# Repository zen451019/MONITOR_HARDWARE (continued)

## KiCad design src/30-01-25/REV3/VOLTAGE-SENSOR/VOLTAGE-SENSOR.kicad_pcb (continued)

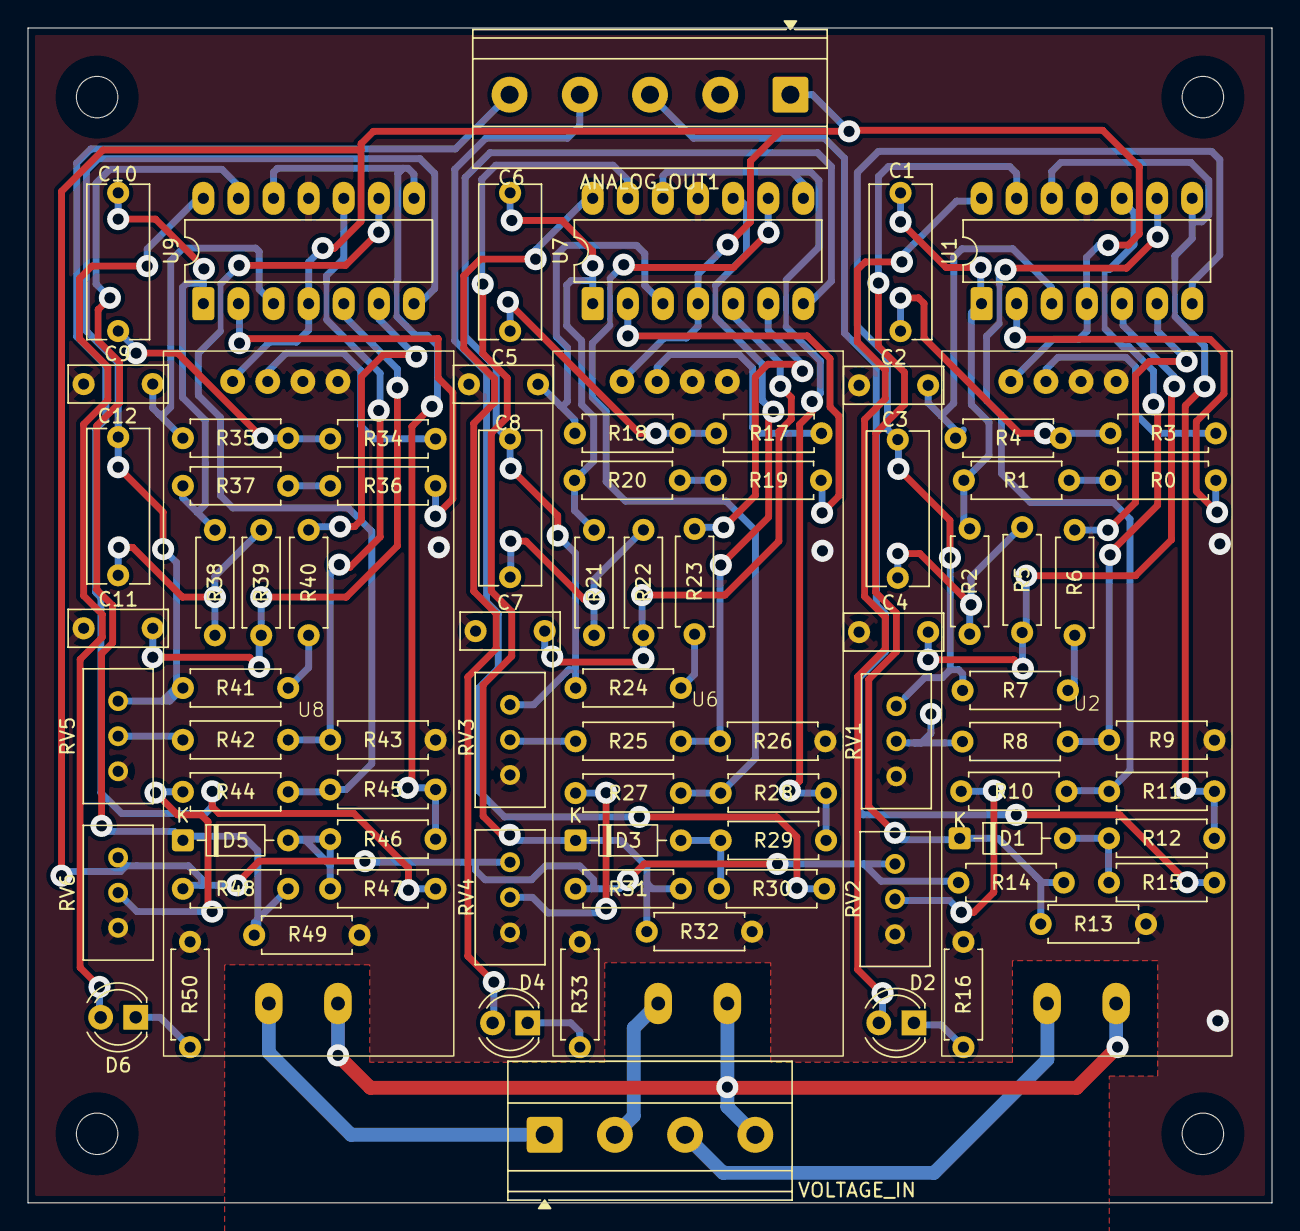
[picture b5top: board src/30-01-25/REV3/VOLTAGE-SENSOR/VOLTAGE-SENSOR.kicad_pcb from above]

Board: 2 copper layers, 90.0 x 85.0 mm, 83 parts (0 on the bottom side), 69 nets.

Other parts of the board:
VOLTAGE_IN: SCREW_TERMINAL_4; TerminalBlock_Phoenix_MKDS-1,5-4-5.08_1x04_P5.08mm_Horizont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

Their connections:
LINE1: VOLTAGE_IN.1; also elsewhere on the board
LINE2: VOLTAGE_IN.2; also elsewhere on the board
LINE3: VOLTAGE_IN.3; also elsewhere on the board
NEUTRAL: VOLTAGE_IN.4; also elsewhere on the board

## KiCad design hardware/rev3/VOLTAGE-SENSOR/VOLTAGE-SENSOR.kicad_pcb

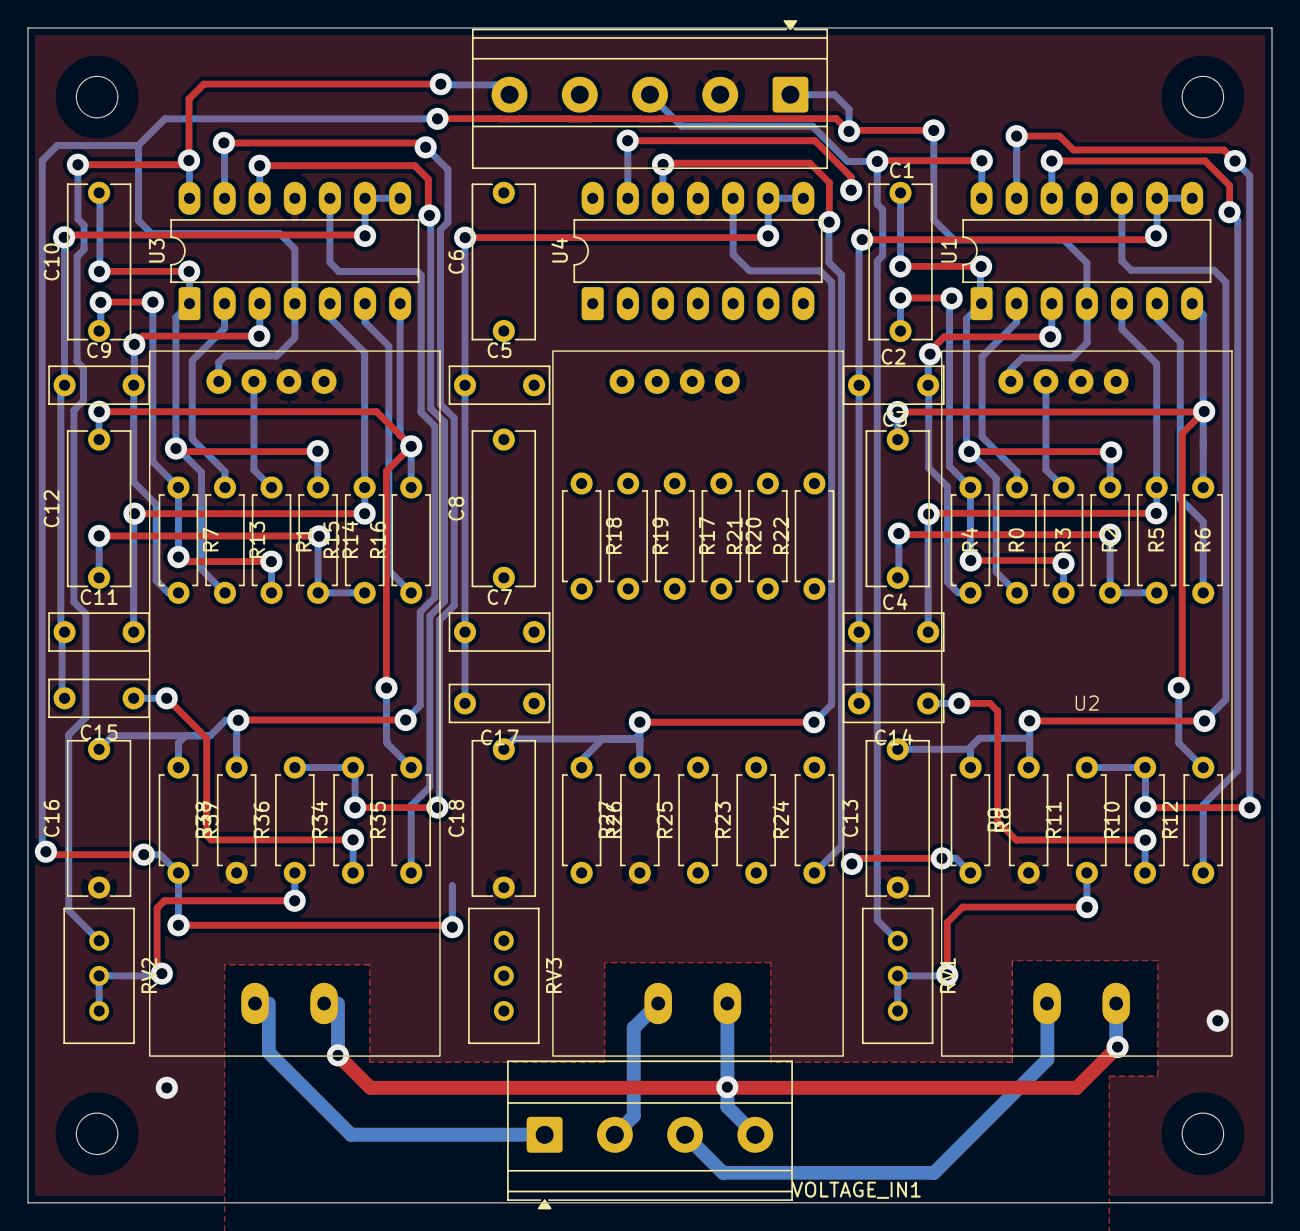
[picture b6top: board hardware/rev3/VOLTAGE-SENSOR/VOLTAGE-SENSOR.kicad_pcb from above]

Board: 2 copper layers, 90.0 x 85.0 mm, 62 parts (0 on the bottom side), 54 nets.

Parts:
ANALOG_OUT1: SCREW_TERMINAL_5; TerminalBlock_Phoenix_MKDS-1,5-5-5.08_1x05_P5.08mm_Horizont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
C1, C3, C6, C8, C10, C12, C13, C16, C18: 100nF; C_Rect_L11.0mm_W4.3mm_P10.00mm_MKT
C2, C4, C5, C7, C9, C11: 15nF; C_Rect_L7.0mm_W2.5mm_P5.00mm
C14, C15, C17: 1uF; C_Rect_L7.0mm_W2.5mm_P5.00mm
R0, R6, R13, R16, R19, R22: 130k; R_Axial_DIN0207_L6.3mm_D2.5mm_P7.62mm_Horizontal
R1, R2, R3, R4, R5, R7, R14, R15, R17, R18, R20, R21: 68k; R_Axial_DIN0207_L6.3mm_D2.5mm_P7.62mm_Horizontal
R8, R9, R26, R27, R37, R38: 100k; R_Axial_DIN0207_L6.3mm_D2.5mm_P7.62mm_Horizontal
R10, R23, R34: 10k; R_Axial_DIN0207_L6.3mm_D2.5mm_P7.62mm_Horizontal
R11, R25, R36: 1k; R_Axial_DIN0207_L6.3mm_D2.5mm_P7.62mm_Horizontal
R12, R24, R35: 5.1k; R_Axial_DIN0207_L6.3mm_D2.5mm_P7.62mm_Horizontal
RV1, RV2, RV3: 10k; Potentiometer_Bourns_3296W_Vertical
U1, U3, U4: LM324; DIP-14_W7.62mm_LongPads
U2, U6, U8: zmpt101b; ZMPT101B
VOLTAGE_IN1: SCREW_TERMINAL_4; TerminalBlock_Phoenix_MKDS-1,5-4-5.08_1x04_P5.08mm_Horizont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

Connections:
5V: ANALOG_OUT1.1, R8.2, R26.2, R37.2, U1.4 (V+), U2.5 (VCC), U3.4 (V+), U4.4 (V+), U6.5 (VCC), U8.5 (VCC)
GND: ANALOG_OUT1.2, C13.1, C16.1, C18.1, R9.1, R27.1, R38.1, U1.11 (V-), U2.3 (GND), U2.4 (GND), U3.11 (V-), U4.11 (V-), U6.3 (GND), U6.4 (GND), U8.3 (GND), U8.4 (GND)
LINE1: U8.1 (L), VOLTAGE_IN1.1
LINE2: U6.1 (L), VOLTAGE_IN1.2
LINE3: U2.1 (L), VOLTAGE_IN1.3
NEUTRAL: U2.2 (N), U6.2 (N), U8.2 (N), VOLTAGE_IN1.4
unnamed: C1.1, R3.2, R4.1
unnamed: C1.2, R0.2, R2.1, U1.1
unnamed: C3.1, R2.2, R5.1
unnamed: C3.2, R6.2, R12.2, U1.7
unnamed: C6.1, R17.2, R18.1
unnamed: C6.2, R19.2, R20.1, U4.1
unnamed: C8.1, R20.2, R21.1
unnamed: C8.2, R22.2, R24.2, U4.7
unnamed: C10.1, R1.2, R7.1
unnamed: C10.2, R13.2, R14.1, U3.1
unnamed: C12.1, R14.2, R15.1
unnamed: C12.2, R16.2, R35.2, U3.7
unnamed: C14.1, R10.1
unnamed: C15.1, R34.1
unnamed: C17.1, R23.1
unnamed: R11.1, RV1.1, RV1.2
unnamed: R25.1, RV3.1, RV3.2
unnamed: R36.1, RV2.1, RV2.2
unnamed: C2.2, R4.2, U1.3 (+)
unnamed: R0.1, U1.2 (-)
unnamed: C4.2, R5.2, U1.5 (+)
unnamed: R6.1, U1.6 (-)
unnamed: C13.2, R8.1, R9.2, U1.10 (+)
unnamed: R12.1, U1.12 (+)
unnamed: R10.2, R11.2, U1.13 (-)
unnamed: C9.2, R7.2, U3.3 (+)
unnamed: R13.1, U3.2 (-)
unnamed: C11.2, R15.2, U3.5 (+)
unnamed: R16.1, U3.6 (-)
unnamed: C16.2, R37.1, R38.2, U3.10 (+)
unnamed: R35.1, U3.12 (+)
unnamed: R34.2, R36.2, U3.13 (-)
unnamed: C5.2, R18.2, U4.3 (+)
unnamed: R19.1, U4.2 (-)
unnamed: C7.2, R21.2, U4.5 (+)
unnamed: R22.1, U4.6 (-)
unnamed: C18.2, R26.1, R27.2, U4.10 (+)
unnamed: R24.1, U4.12 (+)
unnamed: R23.2, R25.2, U4.13 (-)
OUT_S1: R3.1, U2.6 (OUT)
OUT_S2: R17.1, U6.6 (OUT)
OUT_S3: R1.1, U8.6 (OUT)
SIGNAL_OUT1: ANALOG_OUT1.3, RV1.3, U1.14
SIGNAL_OUT2: ANALOG_OUT1.4, RV3.3, U4.14
SIGNAL_OUT3: ANALOG_OUT1.5, RV2.3, U3.14
VGND1: C2.1, C4.1, C14.2, U1.8, U1.9 (-)
VGND2: C5.1, C7.1, C17.2, U4.8, U4.9 (-)
VGND3: C9.1, C11.1, C15.2, U3.8, U3.9 (-)

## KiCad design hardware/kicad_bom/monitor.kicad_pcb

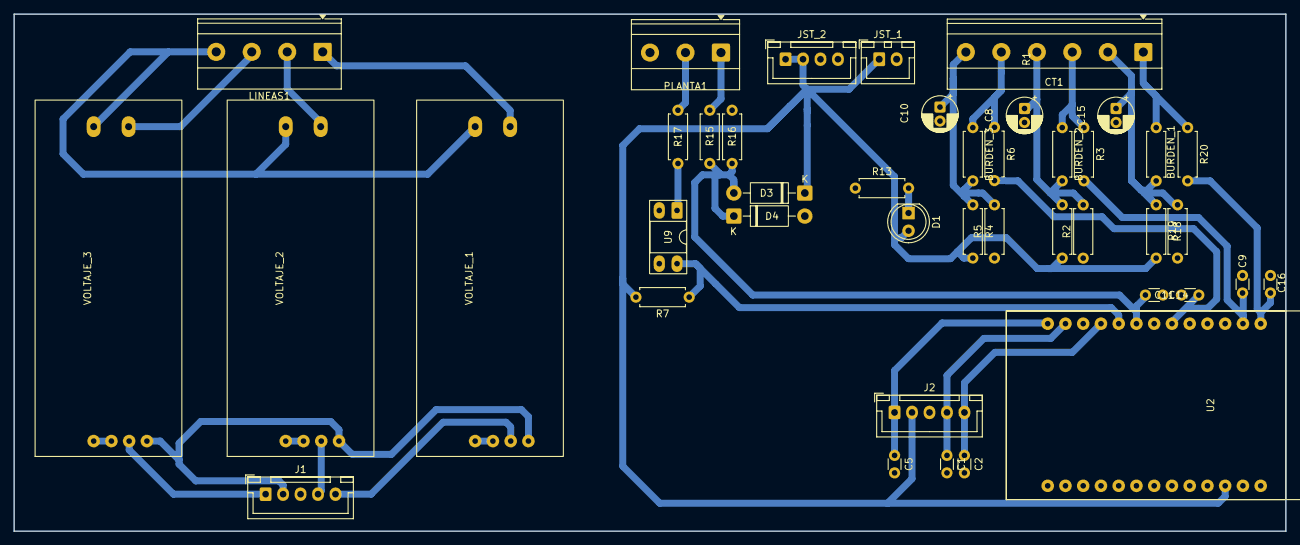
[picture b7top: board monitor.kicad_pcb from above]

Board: 2 copper layers, 182.0 x 74.0 mm, 42 parts (0 on the bottom side), 29 nets.

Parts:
BURDEN_1, BURDEN_2, BURDEN_3: 20; R_Axial_DIN0207_L6.3mm_D2.5mm_P7.62mm_Horizontal
C1, C2, C5, C9, C11, C14, C16: 100nF; C_Disc_D3.0mm_W1.6mm_P2.50mm
C8, C10, C15: 10uF; CP_Radial_D5.0mm_P2.00mm
CT1: Screw_Terminal_01x06; TerminalBlock_Phoenix_MKDS-1,5-6-5.08_1x06_P5.08mm_Horizont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
D1: LED; LED_D5.0mm
D3, D4: 1N5819; D_DO-41_SOD81_P10.16mm_Horizontal
J1: JST_PLACA_ALTERNA; JST_XH_B5B-XH-A_1x05_P2.50mm_Vertical
J2: JST_PLACA_PRINCIPAL; JST_XH_B5B-XH-A_1x05_P2.50mm_Vertical
JST_1: Conn_01x02; JST_XH_B2B-XH-A_1x02_P2.50mm_Vertical
JST_2: Conn_01x04; JST_XH_B4B-XH-A_1x04_P2.50mm_Vertical
LINEAS1: Screw_Terminal_01x04; TerminalBlock_Phoenix_MKDS-1,5-4-5.08_1x04_P5.08mm_Horizont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
PLANTA1: Screw_Terminal_01x03; TerminalBlock_Phoenix_MKDS-1,5-3-5.08_1x03_P5.08mm_Horizont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
R1, R2, R4, R5, R7, R15, R18, R19: 10k; R_Axial_DIN0207_L6.3mm_D2.5mm_P7.62mm_Horizontal
R3, R6, R20: 1k; R_Axial_DIN0207_L6.3mm_D2.5mm_P7.62mm_Horizontal
R13: 150; R_Axial_DIN0207_L6.3mm_D2.5mm_P7.62mm_Horizontal
R16: 3.3k; R_Axial_DIN0207_L6.3mm_D2.5mm_P7.62mm_Horizontal
R17: 1.2K; R_Axial_DIN0207_L6.3mm_D2.5mm_P7.62mm_Horizontal
U2: ttgo_lora32
U9: PC817; DIP-4_W7.62mm_Socket_LongPads
VOLTAJE_1, VOLTAJE_2, VOLTAJE_3: zmpt101b; ZMPT101B

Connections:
3.3V: D1.2 (A), D3.1 (K), J2.2, JST_1.1, JST_2.1, JST_2.2, R1.2, R4.2, R7.2, R19.2, U2.11 (3.3V)
3.3V_PA: J1.2, VOLTAJE_1.5 (VCC), VOLTAJE_2.5 (VCC), VOLTAJE_3.5 (VCC)
BATERIA: PLANTA1.1, R15.1
CT_DOWN_1: BURDEN_1.2, C15.1, CT1.2, R18.2, R19.1
CT_DOWN_2: BURDEN_2.2, C8.1, CT1.4, R1.1, R2.2
CT_DOWN_3: BURDEN_3.2, C10.1, CT1.6, R4.1, R5.2
CT_UP_1: BURDEN_1.1, CT1.1, R20.1
CT_UP_2: BURDEN_2.1, CT1.3, R3.1
CT_UP_3: BURDEN_3.1, CT1.5, R6.1
CURRENT1: C16.2, R20.2, U2.26 (25)
CURRENT2: C9.2, R3.2, U2.25 (04)
CURRENT3: C11.2, R6.2, U2.21 (13)
GND: C1.2, C2.2, C5.2, C8.2, C9.1, C10.2, C11.1, C14.1, C15.2, C16.1, D4.2 (A), J2.3, JST_1.2, JST_2.3, JST_2.4, PLANTA1.3, R2.1, R5.1, R13.1, R16.2, R18.1, U2.12 (GND), U9.2, U9.3
GND1: J1.3, VOLTAJE_1.3 (GND), VOLTAJE_1.4 (GND), VOLTAJE_2.3 (GND), VOLTAJE_2.4 (GND), VOLTAJE_3.3 (GND), VOLTAJE_3.4 (GND)
LINEA1: LINEAS1.1, VOLTAJE_1.1 (L)
LINEA2: LINEAS1.2, VOLTAJE_2.1 (L)
LINEA3: LINEAS1.3, VOLTAJE_3.1 (L)
NIVEL_BATERIA: C14.2, D3.2 (A), D4.1 (K), R15.2, R16.1, U2.19 (14)
NUETRO: LINEAS1.4, VOLTAJE_1.2 (N), VOLTAJE_2.2 (N), VOLTAJE_3.2 (N)
unnamed: D1.1 (K), R13.2
unnamed: R17.2, U9.1
PLANTA_ON: R7.1, U2.18 (35), U9.4
PLANTA_ON_E: PLANTA1.2, R17.1
VOLTAGE1: C2.1, J2.5, U2.17 (34)
VOLTAGE1_PA: J1.5, VOLTAJE_1.6 (OUT)
VOLTAGE2: C1.1, J2.4, U2.15 (39)
VOLTAGE2_PA: J1.4, VOLTAJE_2.6 (OUT)
VOLTAGE3: C5.1, J2.1, U2.14 (36)
VOLTAGE3_PA: J1.1, VOLTAJE_3.6 (OUT)

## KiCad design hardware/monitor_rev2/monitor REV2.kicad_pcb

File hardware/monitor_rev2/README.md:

# MODBUS MASTER MONITOR

## Description
This PCB uses an ESP32 TTGO LoRa V2.1 that functions as a Modbus master and acts as a gateway for Modbus slaves with various integrated sensors. The design includes a UART to RS485 transceiver for network communication using the Modbus protocol. Additionally, it integrates a voltage detector for a 12-volt battery, a multipurpose digital input, and an 8-position DIP switch for Modbus address selection.

## Repository Contents
- `monitor_REV2/` folder: KiCad files for the schematic and PCB.
- `docs/` folder: Diagrams, images, and PDFs of the design.

## Schematic

## PCB

## Manufacturing
### Gerber Files
The Gerber files are in `monitor_REV2/output`.

### Bill of Materials (BOM)
Included as `monitor_REV2/monitor REV2.csv`.

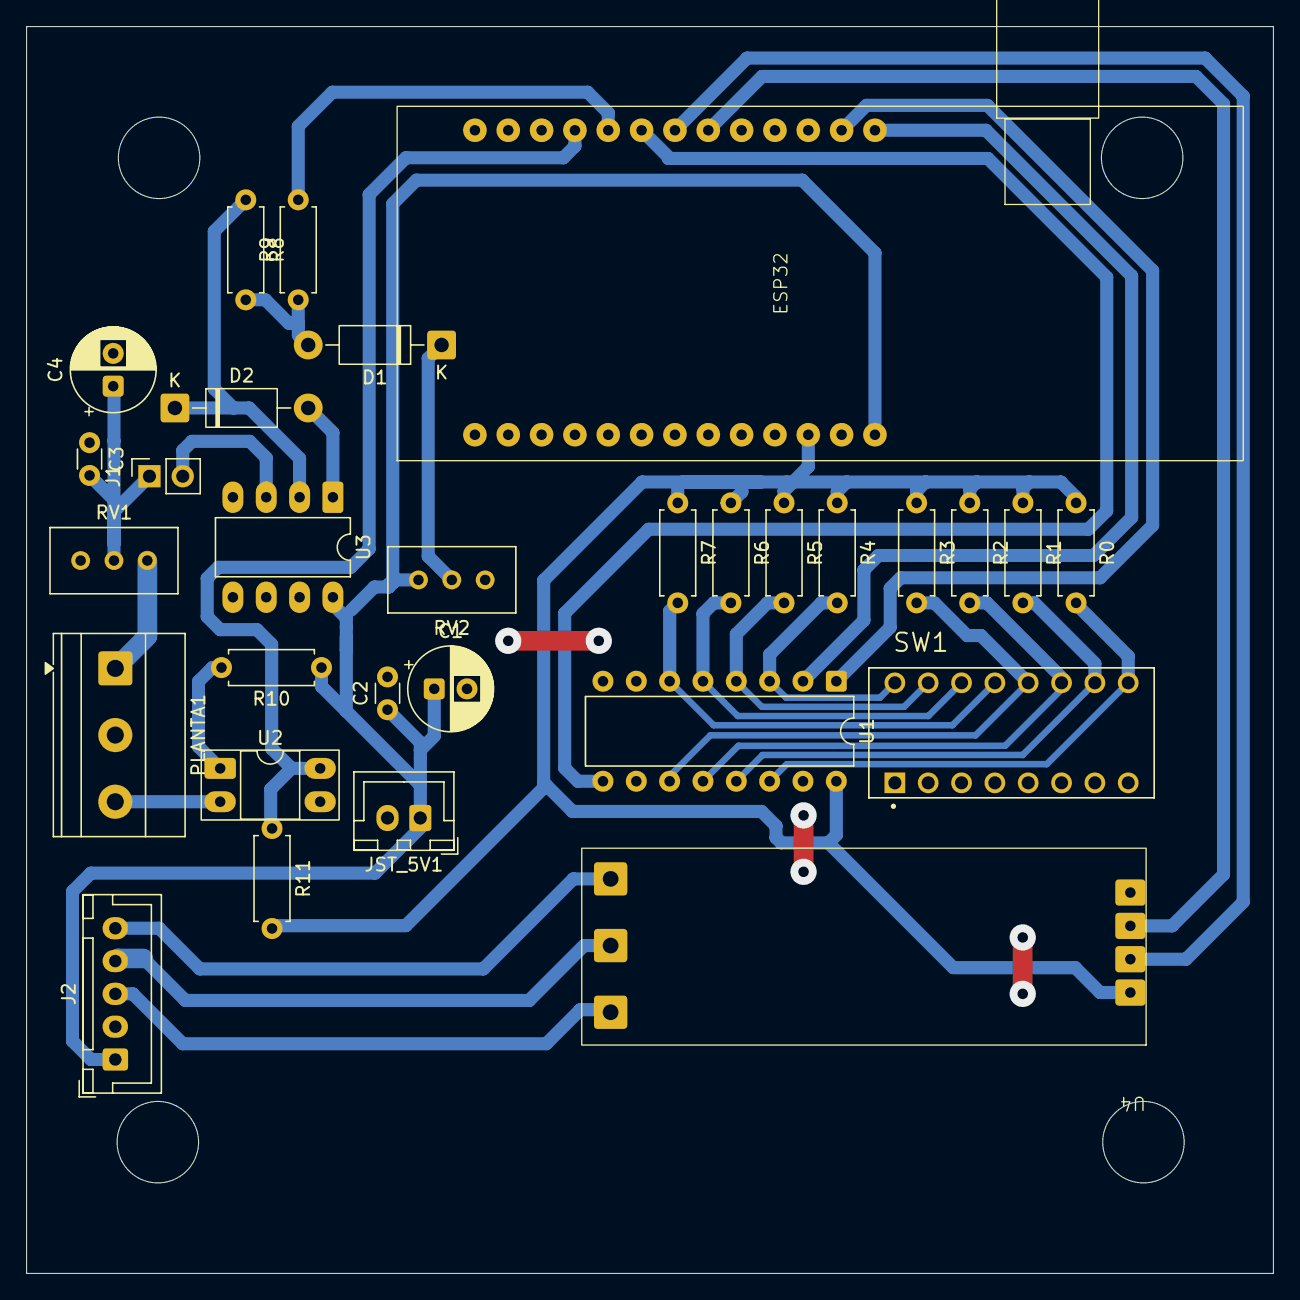
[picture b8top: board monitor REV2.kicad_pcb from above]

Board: 2 copper layers, 95.0 x 95.0 mm, 30 parts (0 on the bottom side), 30 nets.

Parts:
C1, C4: 100uF; CP_Radial_D6.3mm_P2.50mm
C2, C3: 100nF; C_Disc_D3.0mm_W1.6mm_P2.50mm
D1, D2: 1N5819; D_DO-41_SOD81_P10.16mm_Horizontal
ESP32: ttgo_lora32
J1: Conn_01x02_Pin; PinSocket_1x02_P2.54mm_Vertical
J2: Conn_01x05; JST_XH_B5B-XH-A_1x05_P2.50mm_Vertical
JST_5V1: Conn_01x02; JST_XH_B2B-XH-A_1x02_P2.50mm_Vertical
PLANTA1: Screw_Terminal_01x03; TerminalBlock_Phoenix_MKDS-1,5-3-5.08_1x03_P5.08mm_Horizont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
R0, R1, R2, R3, R4, R5, R6, R7, R11: 10k; R_Axial_DIN0207_L6.3mm_D2.5mm_P7.62mm_Horizontal
R8, R9: 100k; R_Axial_DIN0207_L6.3mm_D2.5mm_P7.62mm_Horizontal
R10: 1.2k; R_Axial_DIN0207_L6.3mm_D2.5mm_P7.62mm_Horizontal
RV1, RV2: R_Potentiometer; Potentiometer_Bourns_3296W_Vertical
SW1: SW_DIP_x08; SW_DS01C-254-S-08BE
U1: 74HC165; DIP-16_W7.62mm
U2: PC817; DIP-4_W7.62mm_Socket_LongPads
U3: LM358; DIP-8_W7.62mm_LongPads
U4: XY-017

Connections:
+3.3V: ESP32.11 (3.3V), R0.1, R1.1, R2.1, R3.1, R4.1, R5.1, R6.1, R7.1, R11.2, U1.16 (VCC), U4.1 (VCC)
+5V: C1.1, C2.1, ESP32.13 (5V), J2.1, JST_5V1.1, R10.1, RV2.1, U3.8 (V+)
A+: J2.3, U4.5 (A)
B-: J2.4, U4.6 (B)
BATERIA: PLANTA1.1, RV1.1
E: J2.5, U4.7 (GND)
GND: C1.2, C2.2, C3.1, C4.2, ESP32.12 (GND), J2.2, JST_5V1.2, PLANTA1.2, RV1.3, RV2.3, SW1.9, SW1.10, SW1.11, SW1.12, SW1.13, SW1.14, SW1.15, SW1.16, U1.8 (GND), U1.15 (~CE), U2.3, U3.4 (V-), U4.4 (GND)
NIVEL_BATERIA: ESP32.18 (35), R9.2
unnamed: D1.2 (A), R8.2, R9.1
unnamed: D1.1 (K), RV2.2
unnamed: D2.2 (A), U3.1
unnamed: D2.1 (K), R8.1, U3.2 (-)
unnamed: C3.2, C4.1, J1.1, RV1.2
unnamed: J1.2, U3.3 (+)
unnamed: R10.2, U2.1
PIN_DATA: ESP32.19 (14), U1.9 (Q7)
PLANTA_IGN: PLANTA1.3, U2.2
PLANTA_ON: ESP32.17 (34), R11.1, U2.4
Pin_0: R0.2, SW1.8, U1.14 (D3)
Pin_1: R1.2, SW1.7, U1.13 (D2)
Pin_2: R2.2, SW1.6, U1.12 (D1)
Pin_3: R3.2, SW1.5, U1.11 (D0)
Pin_4: R7.2, SW1.4, U1.6 (D7)
Pin_5: R6.2, SW1.3, U1.5 (D6)
Pin_6: R5.2, SW1.2, U1.4 (D5)
Pin_7: R4.2, SW1.1, U1.3 (D4)
RX: ESP32.21 (13), U4.3 (RXD)
TX: ESP32.20 (12), U4.2 (TXD)
clockPin: ESP32.26 (25), U1.2 (CP)
latchPin: ESP32.25 (04), U1.1 (~PL)

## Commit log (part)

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2025-08-21 Replacement of FreeRTOS task-based acquisition sys
    - ADC acquisition task removed
    - Samples are now captured via software ISR
    - Circular queue accumulates sum of values
    - RMS calculation simplified by obtaining the accumulated value directly
    ---
    NOTE: peding for cleaning code
2025-08-21 Data acquisition board Monitor
    single-layer design
2025-08-21 Monitor hardware documentation
2025-08-21 Corrected links and images
2025-08-22 Code cleanup and documentation New data is added to log_test.
2025-08-25 Bit packaging function implemented
    Bit packaging function implemented in current signal data
    ---
    Note: temporary implementation, unification of messages into a single
    pending message
2025-09-03 Implement unified LoRa payload
    This commit introduces a major architectural refactor to improve
    firmware efficiency, robustness, and clarity. The primary change is the
    consolidation of all sensor and status data into a single, unified
    LoRaWAN payload, replacing the previous fragmented message system.
    This approach significantly reduces uplink traffic, simplifies backend
    decoding, and ensures data atomicity.
2025-09-05 Add: Teting codec for new payload decription
    - Implemented a jupiter notebook to decypher the message send on the
    payload
    ---
    NOTE: this can work as the base for the the chirpstack codec
2025-09-05 Redesign LoRa payload format
    - Refactored the LoRa message handling system by replacing the fragmented
    payload structure with a unified model. The new design is modular and
    scalable, allowing easier integration of new sensors and message types
    while reducing redundancy and improving maintainability.
2025-09-06 Corrected: battery data
    Battery data was sent as zero unless new data arrived. Fixed now sends
    the data in each payload and changes correctly when new data is
    recorded.
2025-09-08 updated: payload
    - Battery data is now treated like any other sensor data, in search of a
    more standard and scalable format.
    - The screen was redesigned to display more information about the
    payload to be sent.
2025-09-09 updated: payload format
    - payload updated and compatible with current version of the decoder
    - updated documentation on the payload format
2025-09-09 updated documentation
2025-09-10 display task changed and optimized
    - increased I2C communication speed
    - optimized data display screen
2025-09-10 refactor: Improve ISR and task scheduling
    - Replaced `TaskMonitorPin` with a more efficient, debounced hardware
    interrupt.
    - Optimized ADC sampling ISR by removing the internal loop, ensuring
    deterministic execution.
    - Hardened periodic tasks by implementing `vTaskDelayUntil` for accurate
    timing.
2025-10-08 code for reading analog variables with ADS1015
    -RS485 communication needs to be added
2025-10-08 refactor: Combine ADS1015 and Modbus configurations, enhance data handling
2025-10-09 Added: Modbus master example code
2025-10-09 Added: Modbus slave simulator code
    -Master and slave code updated to send and receive messages with 45 registers
2025-10-10 Added: Modbus master code with LORAWAN capability
    -Register size changes in sample codes
2025-10-17 added: modbus tasks
    -unfinished code, pending implementation of Modbus tasks
2025-10-22 Update: TTGO master code
    - Test pending
    - Pending update of ADS115 slave sensor to adapt to TTGO master
2025-10-24 successful initial communication
    - Schedule not responding, pending review
2025-10-24 Successful data transmission master slave
    Pending task: create the LoRaWAN payload
2025-10-24 Successful payload creation
    -Missing: assign unique keys to connect to the LoRaWAN gateway
2025-12-02 release codes
2025-12-03 Documentation for Modbus Monitor Master TTGO
2025-12-03 Modbus Master Monitor Documentation Update
2025-12-03 README updated
2025-12-04 Documentation for Modbus monitor master and slave
2025-12-04 Retrucured Repo
2025-12-04 Add: Modbus Monitor Master PCB documentation
2025-12-30 Added: API for handling Modbus requests
2025-12-30 Added: Disconnection logic, code simplification
2025-12-31 changes to the scheduler
    - Added functions to manage the slave list
2025-12-31 EDER fix
2026-01-07 FIX: Corrected Modbus communication handling in master and slave devices
    - It was identified that the master device was sending data packets with a delay of 3 messages compared to what was reported by the slave.
    - Code is added to the slave device for intensive debugging
    - The error in the Modbus API is identified and corrected by discarding responses backed up in the queue.
2026-01-30 Introduce generic Modbus slave core and ADS-specific data layer
    Reworked firmware architecture to separate concerns between the Modbus RTU slave
    core and the sensor data pipeline.
    The main application now operates as a generic Modbus endpoint that reads from
    a shared buffer, while all ADS1015 configuration, sampling, analysis and RMS
    history tracking are encapsulated in a dedicated library.
2026-01-30 Schematics and monitor control board
2026-02-02 feat: refactor ADS acquisition core
    - **Purpose**: Shared foundation for all ADS-based sensors
    - **Features**:
    - Type-agnostic initialization (ADS1015/ADS1115)
    - Protected helper methods: initADS(), readChannel()
    - Thread-safe data access with FreeRTOS mutex
    - Abstract interface enforcing begin() and startSampling()
2026-02-02 chore: move RS485 slave firmware to new structure
2026-02-02 chore: remove documentation artifacts from master
2026-02-02 Deterministic epoch-based scheduler
    -Aligns nextSampleTime to a common epoch to synchronize periods.
    -Orders the scheduler by interval, slaveID, and sensorID.
    -Reschedules without drift (interval skips).
    -Reorders dynamically when sensors are added.
2026-02-04 Added: Pro sensor priority system
    - The system reserves the right to initiate communication to high-priority sensors known as bus drivers.
    - The low-priority sensors, known as passengers, arrive and will be stored in memory until a driver arrives.
    - When a driver arrives, it waits a grace period to wait for its complementary sensor, if there is one.
    - Once the time has passed, it takes the waiting passengers and sends them to the driver.
    - A timeout period is implemented to send passengers if, for any reason, drivers do not arrive.
2026-02-06 Added: Base code for temperature sensor
    -It's just the shell, waiting for the full logic to be implemented.
2026-02-06 Refactor: Sensor abstraction through inheritance
    - Extracted common I2C logic to ADSBase abstract class.
    - Standardized public interface for generic sensor usage in main.
    - Decoupled application logic from specific sensor implementation (RMS/Temp).
2026-02-07 Macros for conditional compilation
    - Implementation of macros to change the object to compile (temperature, voltage/current)
2026-02-07 refactor: move processing params to managers
    - ADSBaseConfig now only contains: type, i2c_addr, gain, process_interval_ms
    - num_channels & conversion_factors moved to ADSManagerConfig
    - Cleaner separation between hardware config and processing logic
2026-02-10 Add pressure sensor support to polymorphic main
    - Introduced pressure sensor reader object
    - Integrated with existing temperature and voltage/current sensors
    - Maintains compile-time polymorphic main and common Modbus data path
2026-02-10 Handling the missing I2C sensor at startup
    - Detects I2C communication failure during initialization
    - Skips sensor read and buffer fill tasks when sensor is absent
    - Fills data buffer with 0xFF to signal error to the master
    - Runtime handling and restart logic pending
2026-03-14 Change: reading data by polling
2026-06-04 PCB light intensity meter
    - Preliminary implementation of Modbus LoRaWAN master
2026-06-05 Minor changes to Modbus master
2026-06-05 refactor: table-driven Modbus polling with static request config
    Replace the dynamic auto-discovery, scheduler, and aggregator tasks
    with a single polling loop driven by a static request table.
    Changes:
    - New ModbusConfig.h: bus config, per-device overrides, and request table
    - ModbusAPI: accept baud rate and UART config parameters
    - main.cpp reduced ~70% (1192 to 347 lines):
2026-06-06 Changes to the PCB
    - DEV_MODULE_EXAPLE_SLAVE added
2026-06-06 refactor: strip ADC acquisition, add simulated sensor slave
    - Remove all ADS/I2C acquisition logic (ADSBase, ADSManager,
    TempADSManager, PressADSManager headers and sources)
    - Replace with simulated sensor task generating V (120V ± 5V)
    and I (5A ± 0.5A) with 120° phase shift between lines
    - Switch to Serial (UART0) with RTS pin 22 for RS485 transceiver
    half-duplex direction control
2026-06-09 fix: pass RTS pin in ModbusServerRTU constructor instead of prepareHardwareSerial
    - ModbusServerRTU now constructed with (2000, 22) so eModbus
    manages GPIO22 as R/D via digitalWrite callback
    - Removed bogus prepareHardwareSerial(Serial, RTS_PIN) call
    that was misinterpreted as bufferSize=22
    - RTS pin is toggled LOW (receive) at idle and HIGH (transmit)
    before each response, fixing bus contention
2026-06-09 Modbus communication correction
    -Error in sending a package via LoRaWan pending correction
2026-06-09 fix: 1 registro por solicitud Modbus + Task Notification elimina crash
2026-06-10 feat: sensores analógicos con suavizado + banderas separadas por tipo
2026-06-10 fix: request ID matching prevents stale callback cross-talk
2026-06-12 feat: integrate SDM630MCT energy meter, align slave addressing
    - Add SDM630MCT (slave 10) with V/I/kWh/W/PF readings
    - Change analog module slave ID 1->5, ADC pins 36/39->32/33
    - Drop stale lock files
2026-06-13 feat: add phantom master node for LoRaWAN stress testing
    - Generates synthetic sensor data in same wire format as real master
    - No Modbus/RS485 dependency — pure LoRaWAN bombardment
    - Configurable interval, sensor values and data modes via PhantomConfig.h
    - Supports TTGO LoRa32 V2.1 and T-Beam V1.2 (dual env)
2026-06-16 fix: len byte now represents 4-byte samples, not Modbus reg count
2026-06-16 fix: node phantom len byte now represents 4-byte samples, same patch as master
2026-06-16 feat: arduino phantom sends new-format payload with 8-sensor activated bytes
2026-06-16 refactor: move ARDUINO_LORA under NODES for better organization
2026-06-19 fix: update devaddr, monitor speed, and kiCad visible layers
2026-06-19 fix: add .gitignore to itself and add KiCad backup patterns
2026-06-20 Pending KiCad files
2026-06-27 feat: add DEV_TRIFASICO with swapWordOrder + per-request padding
